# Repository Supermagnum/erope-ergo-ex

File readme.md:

# Europe-ergo
A 94 key ergonomic,split keyboard, panelized.
Its powered by 2X Raspberry pico and linked with two TRRS jacks.
It uses tht components.

The reset switches, TRRS jacks and raspberry pico's  goes on the reverse side of the Pcb's. 

or:
http://www.keyboard-layout-editor.com/#/gists/50db7ea7b0832342d4c734eb985ec16b

The L1/L2 button is to change from  Norwegian QWERTY to Norwegian Dvorak.

Keycaps:
https://github.com/Supermagnum/Europe-ergo/blob/main/keycaps.jpg

PCBway:

Aisler:
https://aisler.net/p/NEFSAHWJ

Firmware:
[https://github.com/Supermagnum/Europe-ergo/tree/main/Europe_ergo_firmware/europe_ergo](https://github.com/Supermagnum/Europe-ergo/tree/main/ergo-firmware/europe_ergo)

Picture:
https://github.com/Supermagnum/erope-ergo-ex/blob/main/Europe-flex.jpg

All mechanical blueprints as pdf files can be exported from the Freecad file.
Freecad can be found for free here:
https://www.freecadweb.org/

Vial:

https://get.vial.today/

PWM1 to PWM 4 controls LED's ( ON/OFF) based by the active layer, and also caps lock and scroll lock active.

Those and the electrical diagram can be found here:
https://github.com/Supermagnum/Europe-ergo/blob/main/Europe-ergo-PCB/schema/Europe-ergo.pdf
The right side has identical outputs for PWM.

Cherry MX switches should fit the PCB'S.

---------
To do:
Make the cutouts closer to the top and bottoms of the double rows.
Make pcb holders in kicad.
Reduce the number of two pin connectors, and label the connections on the Pcb's.

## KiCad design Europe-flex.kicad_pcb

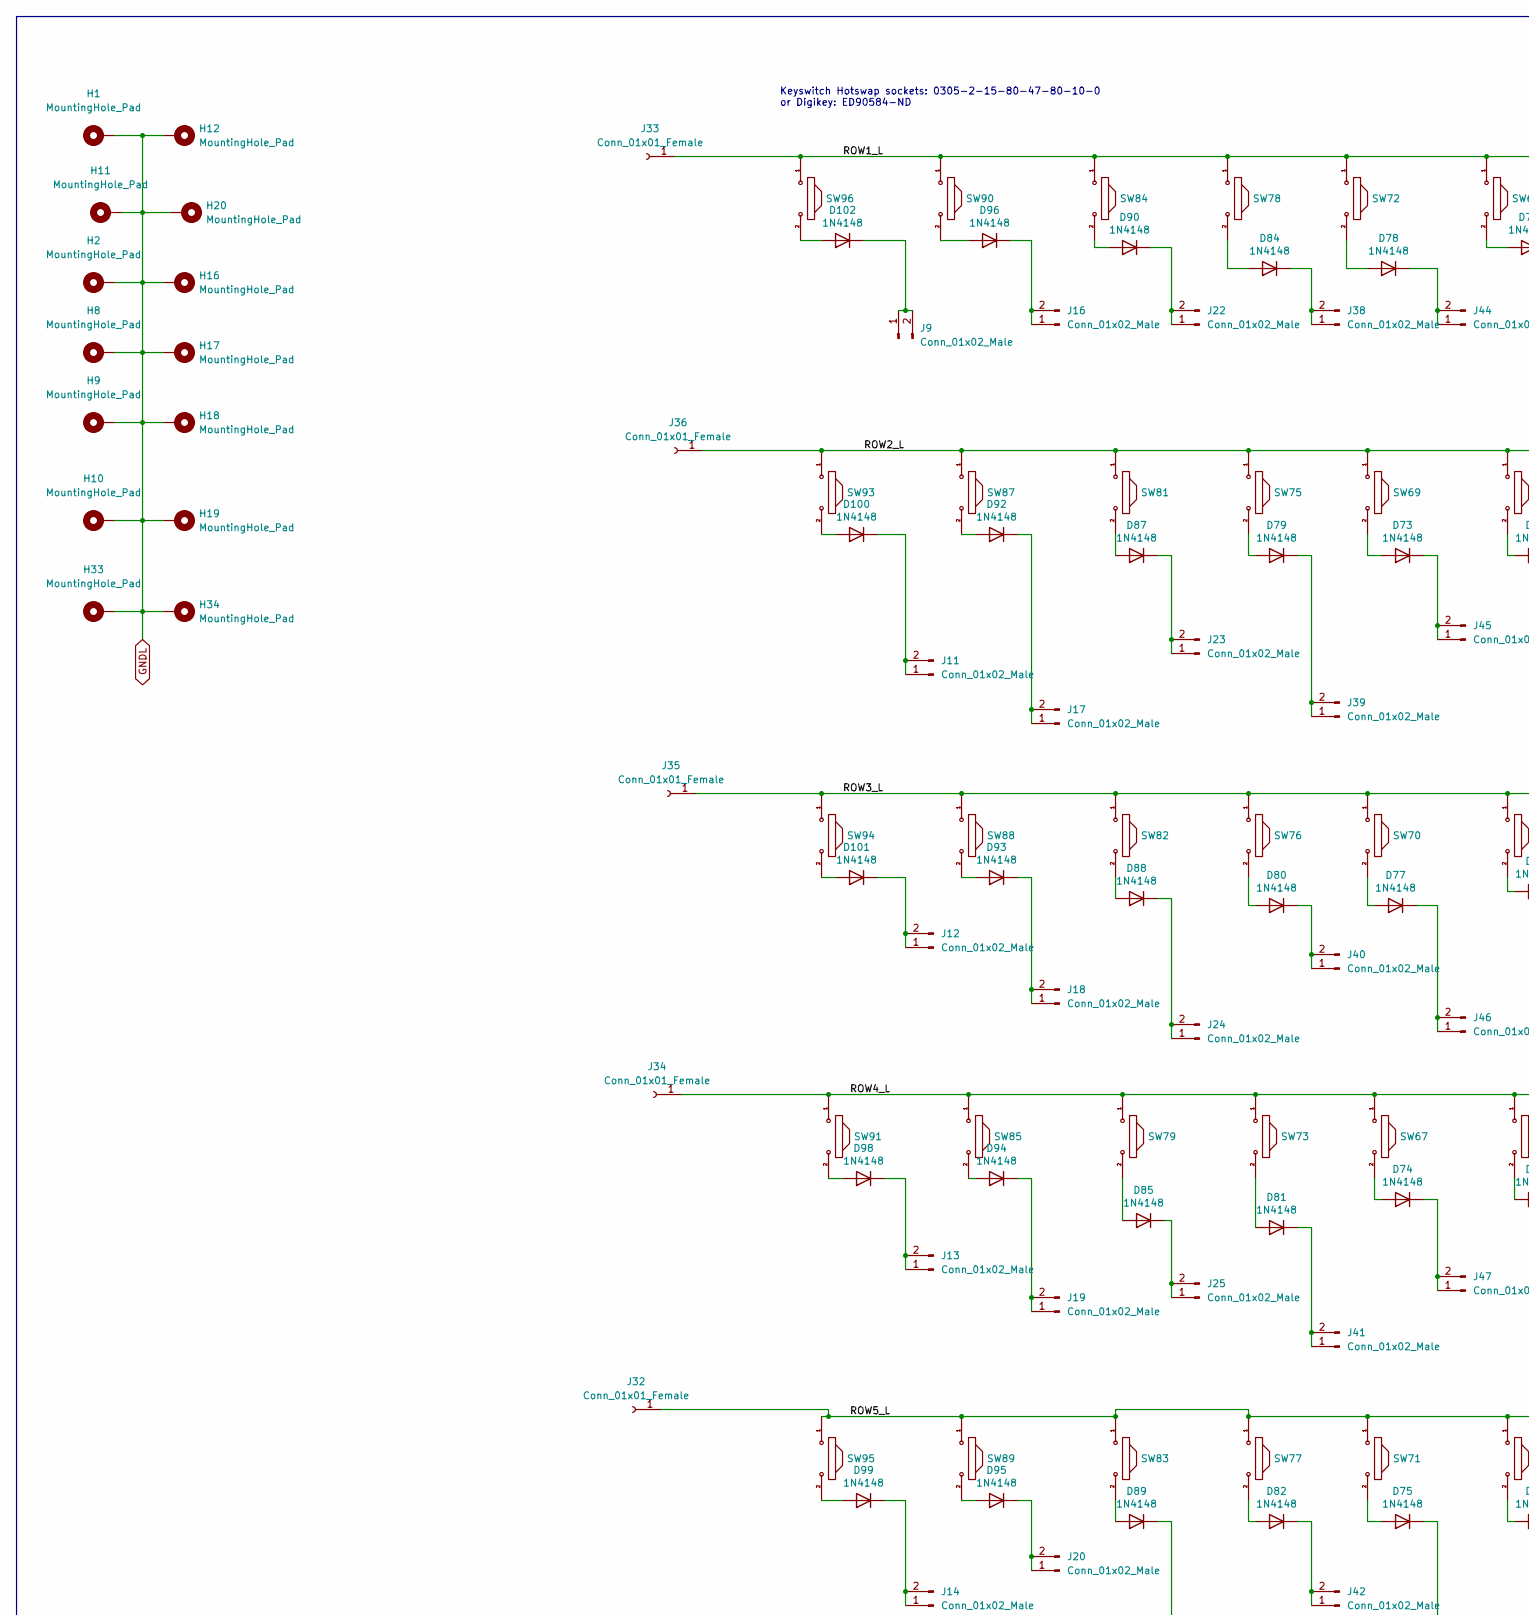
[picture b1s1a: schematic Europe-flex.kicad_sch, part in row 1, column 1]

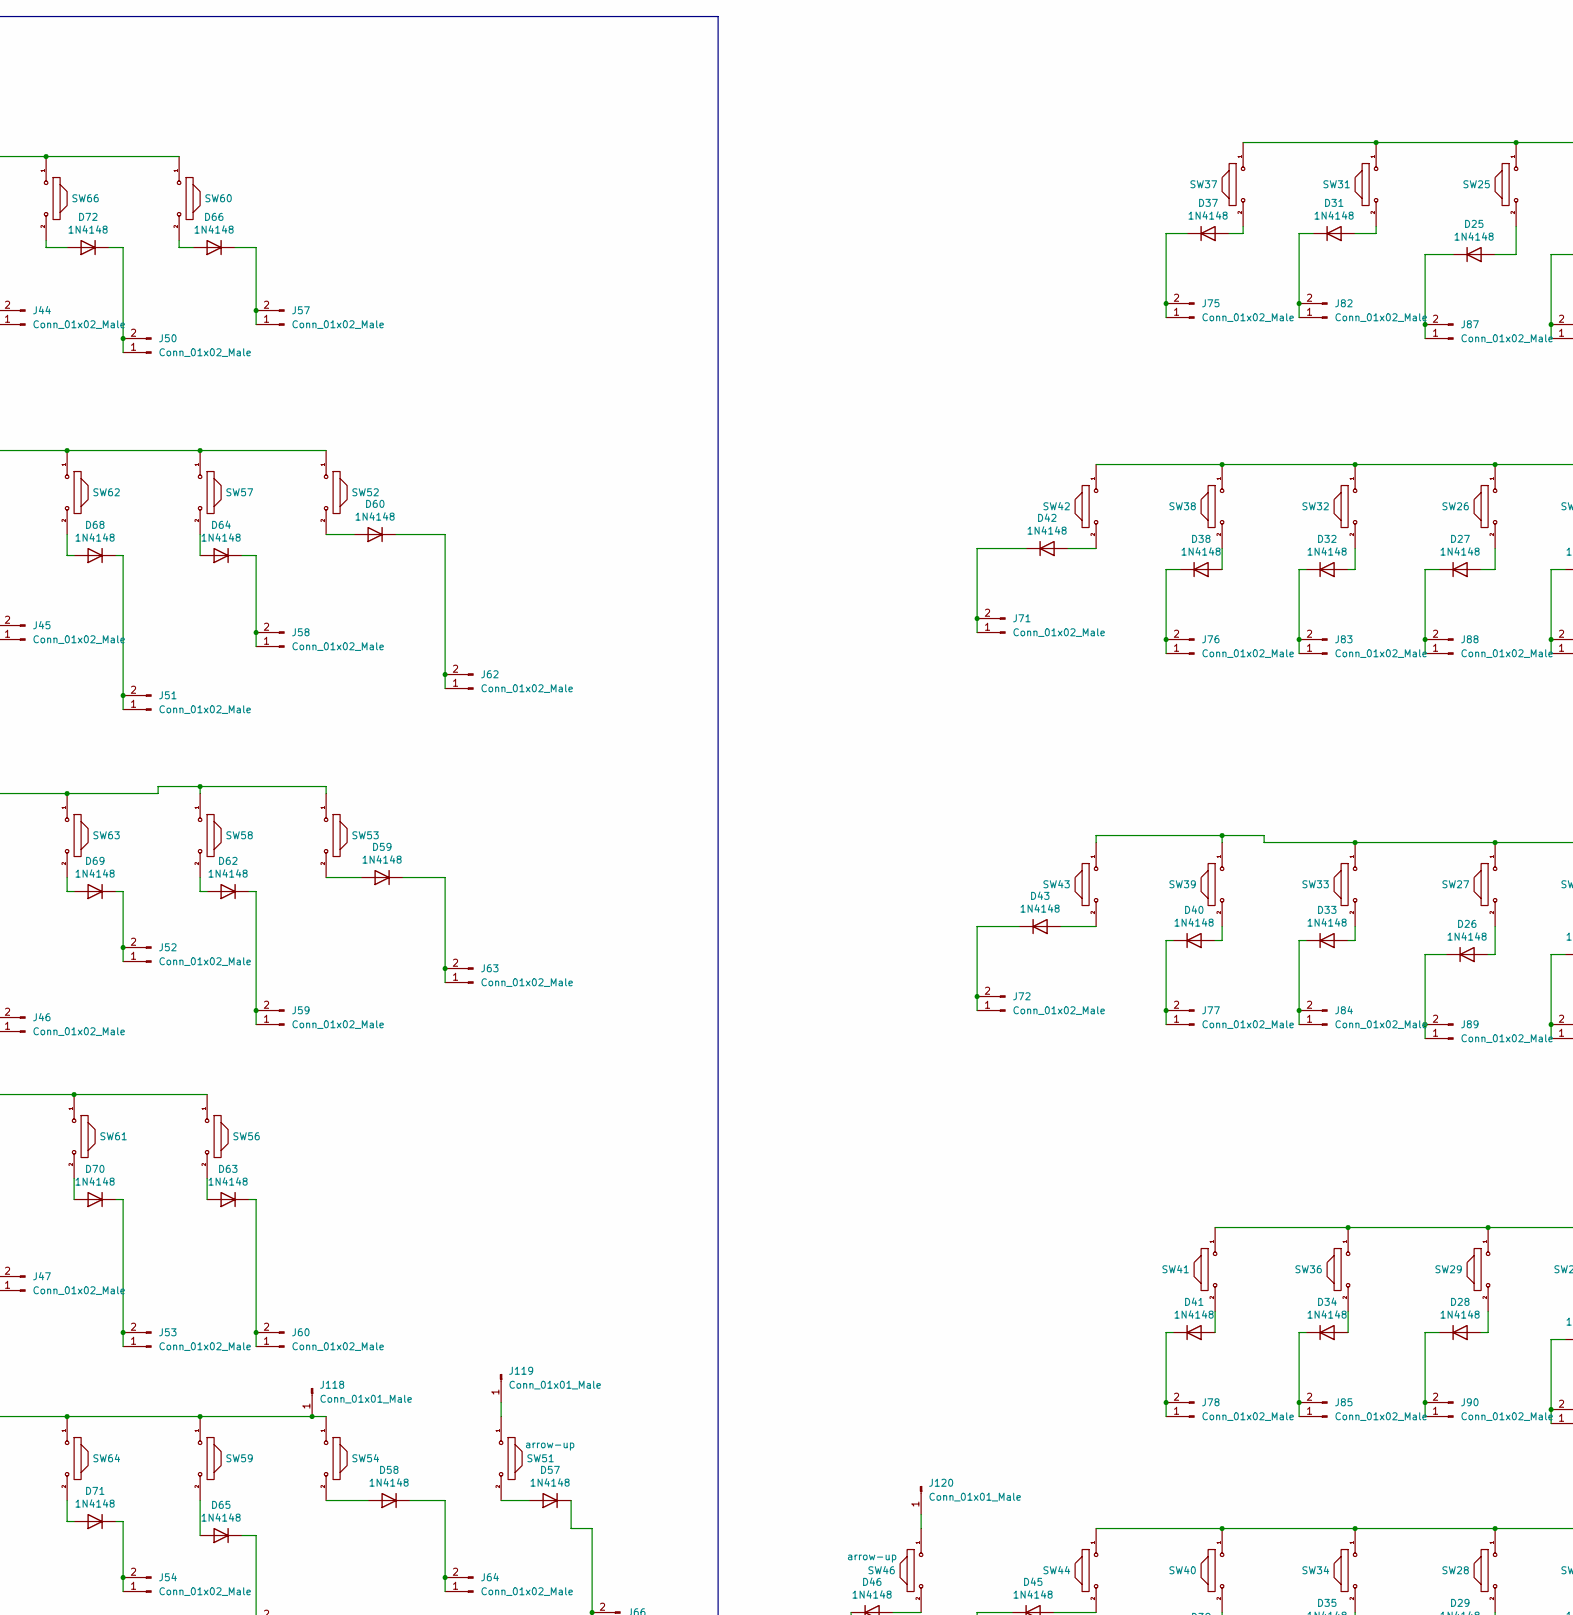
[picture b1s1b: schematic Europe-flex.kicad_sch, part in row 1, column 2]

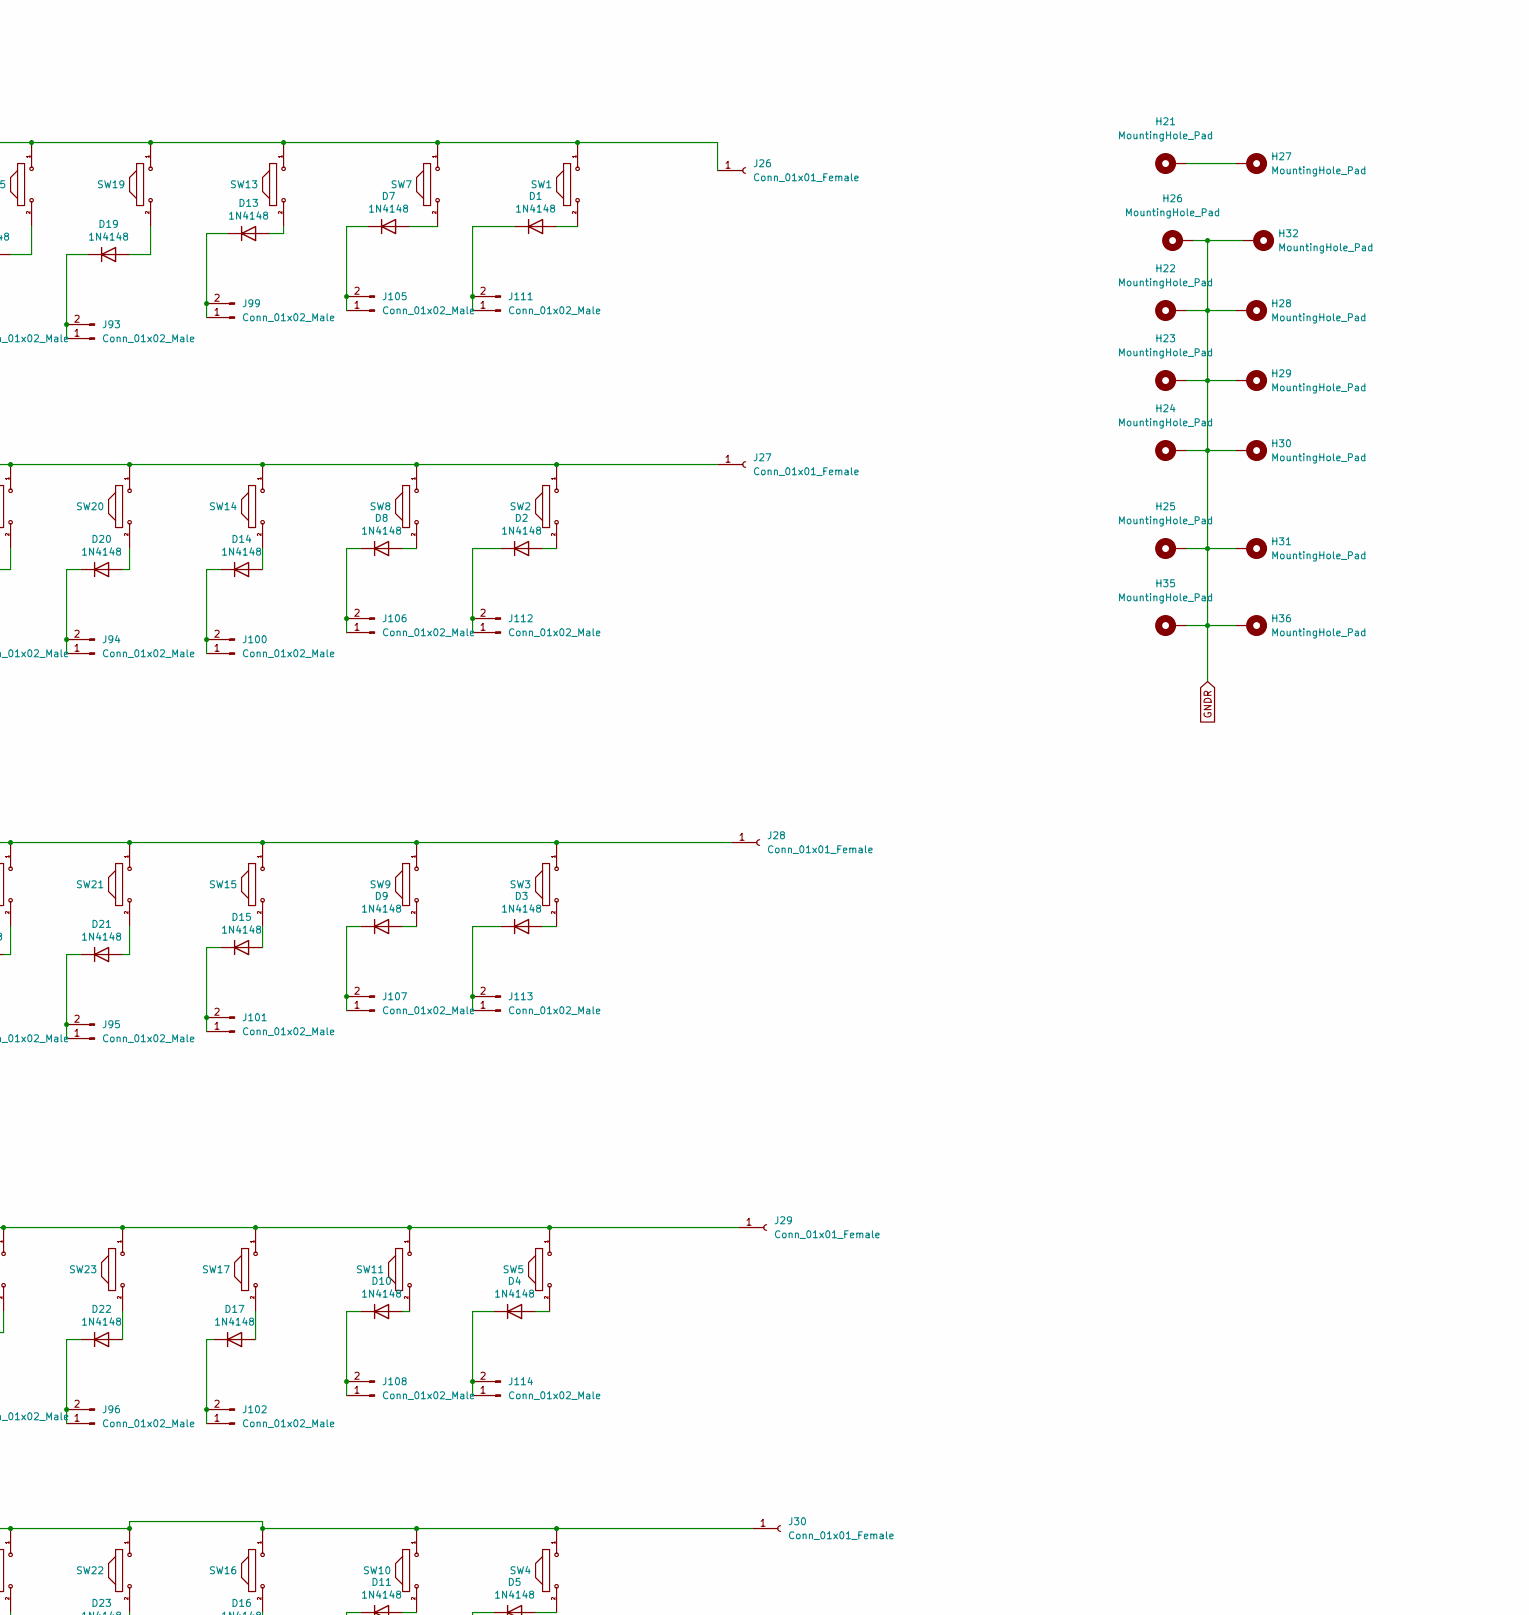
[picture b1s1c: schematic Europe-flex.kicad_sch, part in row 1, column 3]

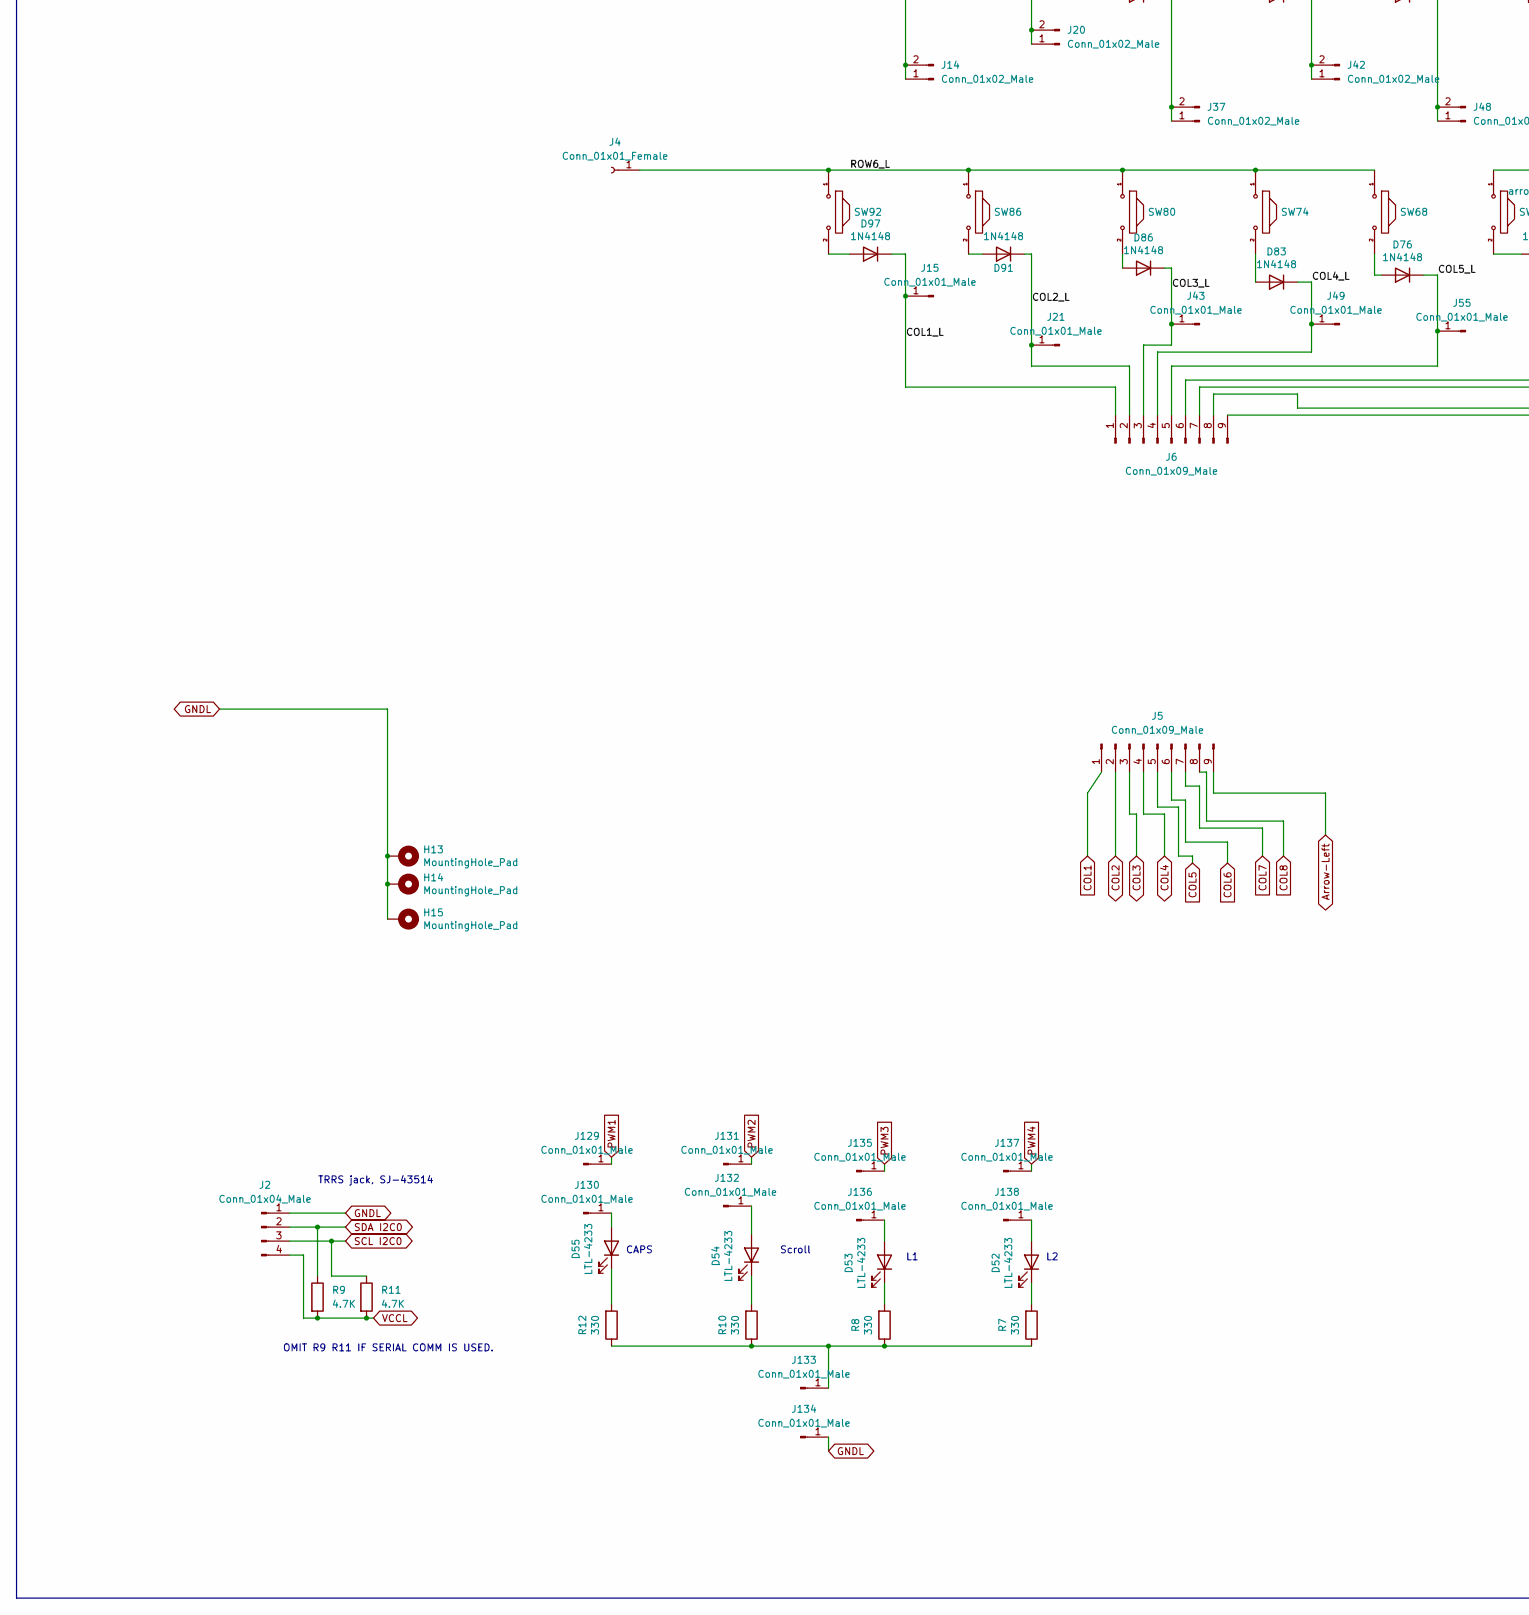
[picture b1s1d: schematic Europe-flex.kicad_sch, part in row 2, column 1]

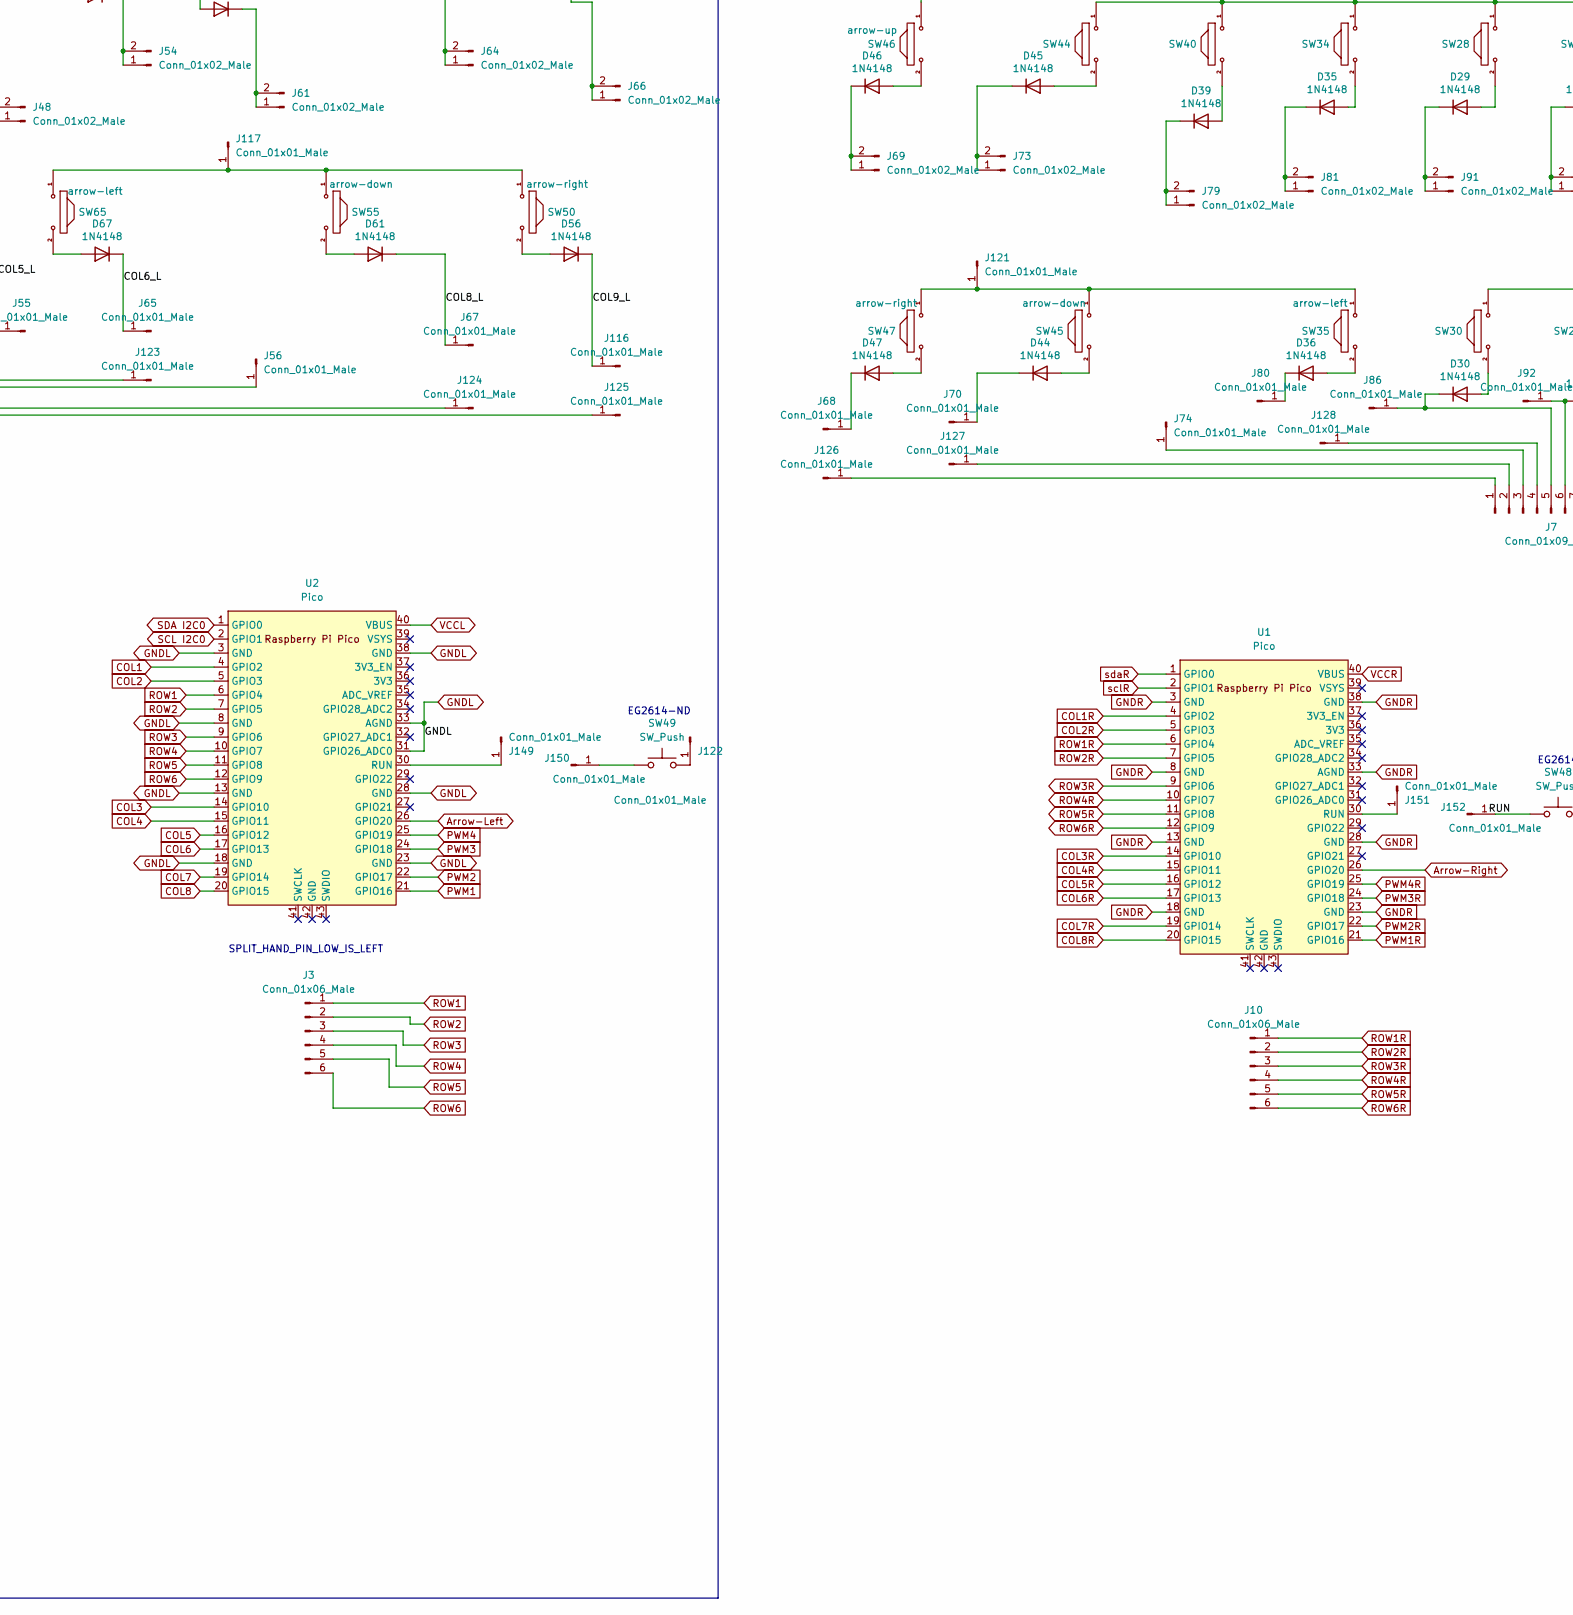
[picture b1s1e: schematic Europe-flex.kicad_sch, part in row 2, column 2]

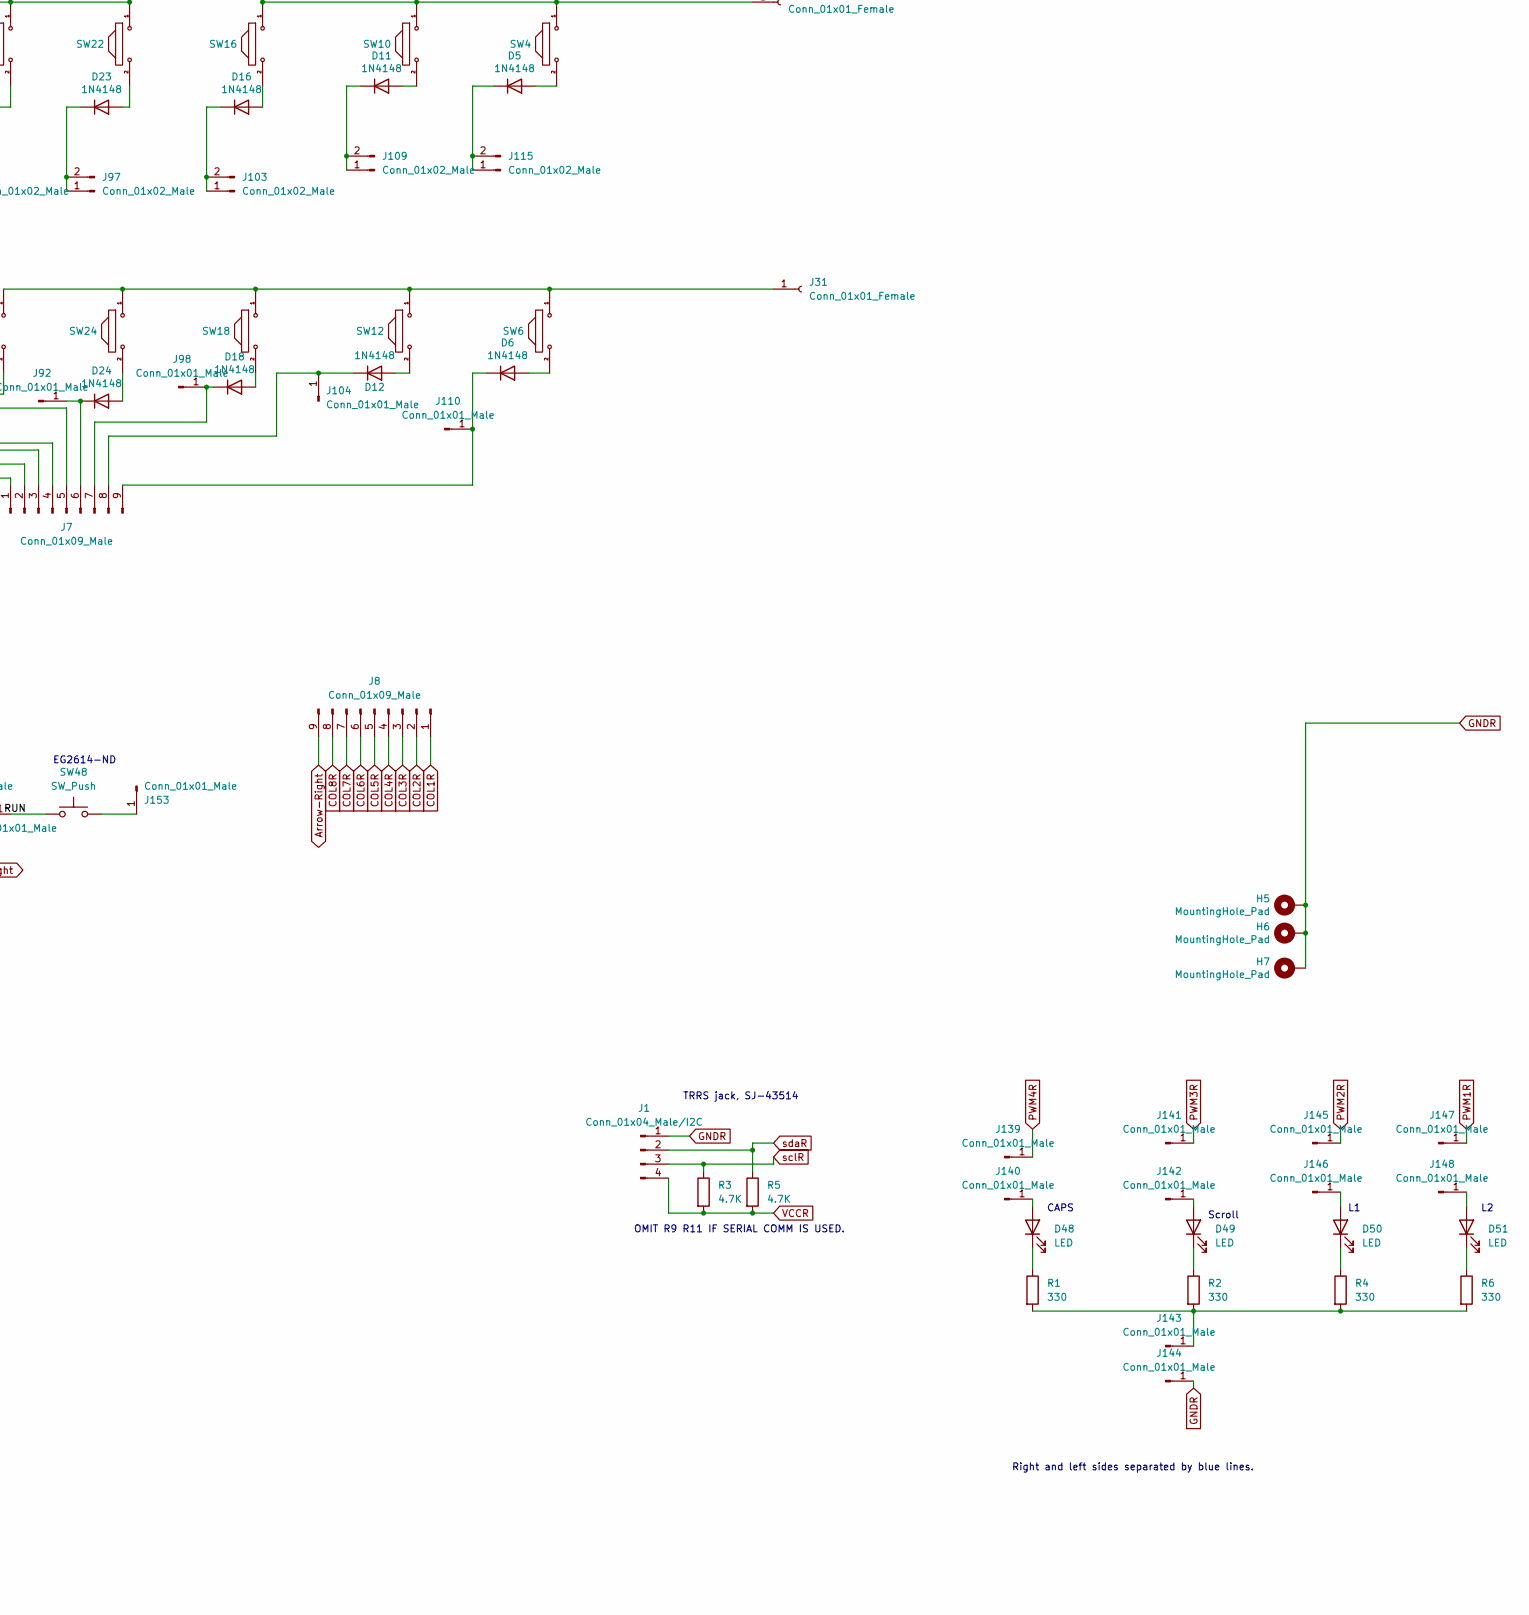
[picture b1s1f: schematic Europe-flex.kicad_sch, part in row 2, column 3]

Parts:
D1, D2, D3, D4, D5, D6, D7, D8, D9, D10, D11, D12, D13, D14, D15, D16, D17, D18, D19, D20, D21, D22, D23, D24, D25, D26, D27, D28, D29, D30, D31, D32, D33, D34, D35, D36, D37, D38, D39, D40, D41, D42, D43, D44, D45, D46, D47, D56, D57, D58, D59, D60, D61, D62, D63, D64, D65, D66, D67, D68, D69, D70, D71, D72, D73, D74, D75, D76, D77, D78, D79, D80, D81, D82, D83, D84, D85, D86, D87, D88, D89, D90, D91, D92, D93, D94, D95, D96, D97, D98, D99, D100, D101, D102: 1N4148; D_DO-35_SOD27_P7.62mm_Horizontal
D48, D49, D50, D51: LED; D_DO-34_SOD68_P2.54mm_Vertical_KathodeUp
D52, D53, D54, D55: LTL-4233; D_A-405_P2.54mm_Vertical_AnodeUp
H1, H2, H5, H6, H7, H8, H9, H10, H11, H12, H13, H14, H15, H16, H17, H18, H19, H20, H21, H22, H23, H24, H25, H26, H27, H28, H29, H30, H31, H32, H33, H34, H35, H36: MountingHole_Pad; MountingHole_4.3mm_M4_DIN965_Pad
J1: Conn_01x04_Male/I2C; CUI_SJ-43514
J2: Conn_01x04_Male; CUI_SJ-43514
J3, J10: Conn_01x06_Male; PinSocket_1x06_P2.54mm_Vertical
J4, J26, J27, J28, J29, J30, J31, J32, J33, J34, J35, J36: Conn_01x01_Female; PinSocket_1x01_P2.54mm_Vertical
J5, J6, J7, J8: Conn_01x09_Male; PinSocket_1x09_P2.54mm_Vertical
J9, J11, J12, J13, J14, J16, J17, J18, J19, J20, J22, J23, J24, J25, J37, J38, J39, J40, J41, J42, J44, J45, J46, J47, J48, J50, J51, J52, J53, J54, J57, J58, J59, J60, J61, J62, J63, J64, J66, J69, J71, J72, J73, J75, J76, J77, J78, J79, J81, J82, J83, J84, J85, J87, J88, J89, J90, J91, J93, J94, J95, J96, J97, J99, J100, J101, J102, J103, J105, J106, J107, J108, J109, J111, J112, J113, J114, J115: Conn_01x02_Male; PinHeader_1x02_P2.54mm_Vertical
J15, J21, J43, J49, J55, J56, J65, J67, J68, J70, J74, J80, J86, J92, J98, J104, J110, J116, J117, J118, J119, J120, J121, J122, J123, J124, J125, J126, J127, J128, J129, J130, J131, J132, J133, J134, J135, J136, J137, J138, J139, J140, J141, J142, J143, J144, J145, J146, J147, J148, J149, J150, J151, J152, J153: Conn_01x01_Male; PinHeader_1x01_P2.54mm_Vertical
R1, R2, R4, R6, R7, R8, R10, R12: 330; R_Axial_DIN0204_L3.6mm_D1.6mm_P5.08mm_Horizontal
R3, R5, R9, R11: 4.7K; R_Axial_DIN0204_L3.6mm_D1.6mm_P5.08mm_Horizontal
SW1, SW6, SW7, SW8, SW9, SW10, SW11, SW12, SW13, SW14, SW15, SW16, SW17, SW18, SW19, SW20, SW21, SW22, SW23, SW24, SW25, SW26, SW27, SW28, SW29, SW30, SW31, SW32, SW33, SW34, SW35, SW36, SW37, SW38, SW39, SW40, SW41, SW42, SW45, SW46, SW47, SW50, SW51, SW52, SW55, SW56, SW57, SW58, SW59, SW60, SW61, SW62, SW63, SW64, SW65, SW66, SW67, SW68, SW69, SW70, SW71, SW72, SW73, SW74, SW75, SW76, SW77, SW78, SW79, SW80, SW81, SW82, SW83, SW84, SW85, SW86, SW87, SW88, SW89, SW90, SW92, SW96: MX-NO-LED; SW_Cherry_MX_1.00u_PCB
SW2, SW3, SW4, SW5, SW43, SW44, SW53, SW54, SW91, SW93, SW94, SW95: MX-NO-LED; SW_Cherry_MX_1.50u_PCB
SW48, SW49: SW_Push; switch_P5.08mm
U1, U2: Pico; RPi_Pico_SMD_TH

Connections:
/COL1_L: D97.1 (K), J6.1, J15.1
/COL2_L: D91.1 (K), J6.2, J21.1
/COL3_L: D86.1 (K), J6.3, J43.1
/COL4_L: D83.1 (K), J6.4, J49.1
/COL5_L: D76.1 (K), J6.5, J55.1
/COL6_L: D67.1 (K), J65.1
/COL8_L: D61.1 (K), J67.1
/COL9_L: D56.1 (K), J116.1
/ROW1_L: J33.1, SW60.1, SW66.1, SW72.1, SW78.1, SW84.1, SW90.1, SW96.1
/ROW2_L: J36.1, SW52.1, SW57.1, SW62.1, SW69.1, SW75.1, SW81.1, SW87.1, SW93.1
/ROW3_L: J35.1, SW53.1, SW58.1, SW63.1, SW70.1, SW76.1, SW82.1, SW88.1, SW94.1
/ROW4_L: J34.1, SW56.1, SW61.1, SW67.1, SW73.1, SW79.1, SW85.1, SW91.1
/ROW5_L: J32.1, J118.1, SW54.1, SW59.1, SW64.1, SW71.1, SW77.1, SW83.1, SW89.1, SW95.1
/ROW6_L: J4.1, SW68.1, SW74.1, SW80.1, SW86.1, SW92.1
Arrow-Left: J5.9, U2.26 (GPIO20)
Arrow-Right: J8.9, U1.26 (GPIO20)
COL1: J5.1, U2.4 (GPIO2)
COL1R: J8.1, U1.4 (GPIO2)
COL2: J5.2, U2.5 (GPIO3)
COL2R: J8.2, U1.5 (GPIO3)
COL3: J5.3, U2.14 (GPIO10)
COL3R: J8.3, U1.14 (GPIO10)
COL4: J5.4, U2.15 (GPIO11)
COL4R: J8.4, U1.15 (GPIO11)
COL5: J5.5, U2.16 (GPIO12)
COL5R: J8.5, U1.16 (GPIO12)
COL6: J5.6, U2.17 (GPIO13)
COL6R: J8.6, U1.17 (GPIO13)
COL7: J5.7, U2.19 (GPIO14)
COL7R: J8.7, U1.19 (GPIO14)
COL8: J5.8, U2.20 (GPIO15)
COL8R: J8.8, U1.20 (GPIO15)
unnamed: D1.1 (K), J111.1, J111.2
unnamed: D1.2 (A), SW1.2
unnamed: D2.1 (K), J112.1, J112.2
unnamed: D2.2 (A), SW2.2
unnamed: D3.1 (K), J113.1, J113.2
unnamed: D3.2 (A), SW3.2
unnamed: D4.1 (K), J114.1, J114.2
unnamed: D4.2 (A), SW5.2
unnamed: D5.1 (K), J115.1, J115.2
unnamed: D5.2 (A), SW4.2
unnamed: D6.1 (K), J7.9, J110.1
unnamed: D6.2 (A), SW6.2
unnamed: D7.1 (K), J105.1, J105.2
unnamed: D7.2 (A), SW7.2
unnamed: D8.1 (K), J106.1, J106.2
unnamed: D8.2 (A), SW8.2
unnamed: D9.1 (K), J107.1, J107.2
unnamed: D9.2 (A), SW9.2
unnamed: D10.1 (K), J108.1, J108.2
unnamed: D10.2 (A), SW11.2
unnamed: D11.1 (K), J109.1, J109.2
unnamed: D11.2 (A), SW10.2
unnamed: D12.1 (K), J7.8, J104.1
unnamed: D12.2 (A), SW12.2
unnamed: D13.1 (K), J99.1, J99.2
unnamed: D13.2 (A), SW13.2
unnamed: D14.1 (K), J100.1, J100.2
unnamed: D14.2 (A), SW14.2
unnamed: D15.1 (K), J101.1, J101.2
unnamed: D15.2 (A), SW15.2
unnamed: D16.1 (K), J103.1, J103.2
unnamed: D16.2 (A), SW16.2
unnamed: D17.1 (K), J102.1, J102.2
unnamed: D17.2 (A), SW17.2
unnamed: D18.1 (K), J7.7, J98.1
unnamed: D18.2 (A), SW18.2
unnamed: D19.1 (K), J93.1, J93.2
unnamed: D19.2 (A), SW19.2
unnamed: D20.1 (K), J94.1, J94.2
unnamed: D20.2 (A), SW20.2
unnamed: D21.1 (K), J95.1, J95.2
unnamed: D21.2 (A), SW21.2
unnamed: D22.1 (K), J96.1, J96.2
unnamed: D22.2 (A), SW23.2
unnamed: D23.1 (K), J97.1, J97.2
unnamed: D23.2 (A), SW22.2
unnamed: D24.1 (K), J7.6, J92.1
unnamed: D24.2 (A), SW24.2
unnamed: D25.1 (K), J87.1, J87.2
unnamed: D25.2 (A), SW25.2
unnamed: D26.1 (K), J89.1, J89.2
unnamed: D26.2 (A), SW27.2
unnamed: D27.1 (K), J88.1, J88.2
unnamed: D27.2 (A), SW26.2
unnamed: D28.1 (K), J90.1, J90.2
unnamed: D28.2 (A), SW29.2
unnamed: D29.1 (K), J91.1, J91.2
unnamed: D29.2 (A), SW28.2
unnamed: D30.1 (K), J7.5, J86.1
unnamed: D30.2 (A), SW30.2
unnamed: D31.1 (K), J82.1, J82.2
unnamed: D31.2 (A), SW31.2
unnamed: D32.1 (K), J83.1, J83.2
unnamed: D32.2 (A), SW32.2
unnamed: D33.1 (K), J84.1, J84.2
unnamed: D33.2 (A), SW33.2
unnamed: D34.1 (K), J85.1, J85.2
unnamed: D34.2 (A), SW36.2
unnamed: D35.1 (K), J81.1, J81.2
unnamed: D35.2 (A), SW34.2
unnamed: D36.1 (K), J80.1
unnamed: D36.2 (A), SW35.2
unnamed: D37.1 (K), J75.1, J75.2
unnamed: D37.2 (A), SW37.2
unnamed: D38.1 (K), J76.1, J76.2
unnamed: D38.2 (A), SW38.2
unnamed: D39.1 (K), J79.1, J79.2
unnamed: D39.2 (A), SW40.2
unnamed: D40.1 (K), J77.1, J77.2
unnamed: D40.2 (A), SW39.2
unnamed: D41.1 (K), J78.1, J78.2
unnamed: D41.2 (A), SW41.2
unnamed: D42.1 (K), J71.1, J71.2
unnamed: D42.2 (A), SW42.2
unnamed: D43.1 (K), J72.1, J72.2
unnamed: D43.2 (A), SW43.2
unnamed: D44.1 (K), J70.1
unnamed: D44.2 (A), SW45.2
unnamed: D45.1 (K), J73.1, J73.2
unnamed: D45.2 (A), SW44.2
unnamed: D46.1 (K), J69.1, J69.2
unnamed: D46.2 (A), SW46.2
unnamed: D47.1 (K), J68.1
unnamed: D47.2 (A), SW47.2
unnamed: D48.1 (K), R1.1
unnamed: D48.2 (A), J140.1
unnamed: D49.1 (K), R2.1
unnamed: D49.2 (A), J142.1
unnamed: D50.1 (K), R4.1
unnamed: D50.2 (A), J146.1
unnamed: D51.1 (K), R6.1
unnamed: D51.2 (A), J148.1
unnamed: D52.1 (K), R7.2
unnamed: D52.2 (A), J138.1
unnamed: D53.1 (K), R8.2
unnamed: D53.2 (A), J136.1
unnamed: D54.1 (K), R10.2
unnamed: D54.2 (A), J132.1
unnamed: D55.1 (K), R12.2
unnamed: D55.2 (A), J130.1
unnamed: D56.2 (A), SW50.2
unnamed: D57.1 (K), J66.1, J66.2
unnamed: D57.2 (A), SW51.2
unnamed: D58.1 (K), J64.1, J64.2
unnamed: D58.2 (A), SW54.2
unnamed: D59.1 (K), J63.1, J63.2
unnamed: D59.2 (A), SW53.2
unnamed: D60.1 (K), J62.1, J62.2
unnamed: D60.2 (A), SW52.2
unnamed: D61.2 (A), SW55.2
unnamed: D62.1 (K), J59.1, J59.2
unnamed: D62.2 (A), SW58.2
unnamed: D63.1 (K), J60.1, J60.2
unnamed: D63.2 (A), SW56.2
unnamed: D64.1 (K), J58.1, J58.2
unnamed: D64.2 (A), SW57.2
unnamed: D65.1 (K), J61.1, J61.2
unnamed: D65.2 (A), SW59.2
unnamed: D66.1 (K), J57.1, J57.2
unnamed: D66.2 (A), SW60.2
unnamed: D67.2 (A), SW65.2
unnamed: D68.1 (K), J51.1, J51.2
unnamed: D68.2 (A), SW62.2
unnamed: D69.1 (K), J52.1, J52.2
unnamed: D69.2 (A), SW63.2
unnamed: D70.1 (K), J53.1, J53.2
unnamed: D70.2 (A), SW61.2
unnamed: D71.1 (K), J54.1, J54.2
unnamed: D71.2 (A), SW64.2
unnamed: D72.1 (K), J50.1, J50.2
unnamed: D72.2 (A), SW66.2
unnamed: D73.1 (K), J45.1, J45.2
unnamed: D73.2 (A), SW69.2
unnamed: D74.1 (K), J47.1, J47.2
unnamed: D74.2 (A), SW67.2
unnamed: D75.1 (K), J48.1, J48.2
unnamed: D75.2 (A), SW71.2
unnamed: D76.2 (A), SW68.2
unnamed: D77.1 (K), J46.1, J46.2
unnamed: D77.2 (A), SW70.2
unnamed: D78.1 (K), J44.1, J44.2
unnamed: D78.2 (A), SW72.2
unnamed: D79.1 (K), J39.1, J39.2
unnamed: D79.2 (A), SW75.2
unnamed: D80.1 (K), J40.1, J40.2
unnamed: D80.2 (A), SW76.2
unnamed: D81.1 (K), J41.1, J41.2
unnamed: D81.2 (A), SW73.2
unnamed: D82.1 (K), J42.1, J42.2
unnamed: D82.2 (A), SW77.2
unnamed: D83.2 (A), SW74.2
unnamed: D84.1 (K), J38.1, J38.2
unnamed: D84.2 (A), SW78.2
unnamed: D85.1 (K), J25.1, J25.2
unnamed: D85.2 (A), SW79.2
unnamed: D86.2 (A), SW80.2
unnamed: D87.1 (K), J23.1, J23.2
unnamed: D87.2 (A), SW81.2
unnamed: D88.1 (K), J24.1, J24.2
unnamed: D88.2 (A), SW82.2
unnamed: D89.1 (K), J37.1, J37.2
unnamed: D89.2 (A), SW83.2
unnamed: D90.1 (K), J22.1, J22.2
unnamed: D90.2 (A), SW84.2
unnamed: D91.2 (A), SW86.2
unnamed: D92.1 (K), J17.1, J17.2
unnamed: D92.2 (A), SW87.2
unnamed: D93.1 (K), J18.1, J18.2
unnamed: D93.2 (A), SW88.2
unnamed: D94.1 (K), J19.1, J19.2
unnamed: D94.2 (A), SW85.2
unnamed: D95.1 (K), J20.1, J20.2
unnamed: D95.2 (A), SW89.2
unnamed: D96.1 (K), J16.1, J16.2
unnamed: D96.2 (A), SW90.2
unnamed: D97.2 (A), SW92.2
unnamed: D98.1 (K), J13.1, J13.2
unnamed: D98.2 (A), SW91.2
unnamed: D99.1 (K), J14.1, J14.2
unnamed: D99.2 (A), SW95.2
unnamed: D100.1 (K), J11.1, J11.2
unnamed: D100.2 (A), SW93.2
unnamed: D101.1 (K), J12.1, J12.2
unnamed: D101.2 (A), SW94.2
unnamed: D102.1 (K), J9.1, J9.2
unnamed: D102.2 (A), SW96.2
unnamed: H21.1, H27.1
unnamed: J7.3, J74.1
unnamed: J26.1, SW1.1, SW7.1, SW13.1, SW19.1, SW25.1, SW31.1, SW37.1
unnamed: J27.1, SW2.1, SW8.1, SW14.1, SW20.1, SW26.1, SW32.1, SW38.1, SW42.1
unnamed: J28.1, SW3.1, SW9.1, SW15.1, SW21.1, SW27.1, SW33.1, SW39.1, SW43.1
unnamed: J29.1, SW5.1, SW11.1, SW17.1, SW23.1, SW29.1, SW36.1, SW41.1
unnamed: J30.1, SW4.1, SW10.1, SW16.1, SW22.1, SW28.1, SW34.1, SW40.1, SW44.1
unnamed: J31.1, SW6.1, SW12.1, SW18.1, SW24.1, SW30.1
unnamed: J6.7, J56.1
unnamed: J117.1, SW50.1, SW55.1, SW65.1
unnamed: J119.1, SW51.1
unnamed: J120.1, SW46.1
unnamed: J121.1, SW35.1, SW45.1, SW47.1
unnamed: J122.1, SW49.2
unnamed: J6.6, J123.1
unnamed: J6.8, J124.1
unnamed: J6.9, J125.1
unnamed: J7.1, J126.1
unnamed: J7.2, J127.1
unnamed: J7.4, J128.1
unnamed: J133.1, R7.1, R8.1, R10.1, R12.1
unnamed: J143.1, R1.2, R2.2, R4.2, R6.2
unnamed: J149.1, U2.30 (RUN)
unnamed: J150.1, SW49.1
unnamed: J151.1, U1.30 (RUN)
unnamed: J152.1, SW48.1
unnamed: J153.1, SW48.2
PWM1: J129.1, U2.21 (GPIO16)
PWM1R: J147.1, U1.21 (GPIO16)
PWM2: J131.1, U2.22 (GPIO17)
PWM2R: J145.1, U1.22 (GPIO17)
PWM3: J135.1, U2.24 (GPIO18)
PWM3R: J141.1, U1.24 (GPIO18)
PWM4: J137.1, U2.25 (GPIO19)
PWM4R: J139.1, U1.25 (GPIO19)
ROW1: J3.1, U2.6 (GPIO4)
ROW1R: J10.1, U1.6 (GPIO4)
ROW2: J3.2, U2.7 (GPIO5)
ROW2R: J10.2, U1.7 (GPIO5)
ROW3: J3.3, U2.9 (GPIO6)
ROW3R: J10.3, U1.9 (GPIO6)
ROW4: J3.4, U2.10 (GPIO7)
ROW4R: J10.4, U1.10 (GPIO7)
ROW5: J3.5, U2.11 (GPIO8)
ROW5R: J10.5, U1.11 (GPIO8)
ROW6: J3.6, U2.12 (GPIO9)
ROW6R: J10.6, U1.12 (GPIO9)
SCL I2C0: J2.3, R11.1, U2.2 (GPIO1)
SDA I2C0: J2.2, R9.1, U2.1 (GPIO0)
VCCL: J2.4, R9.2, R11.2, U2.40 (VBUS)
VCCR: J1.4, R3.2, R5.2, U1.40 (VBUS)
sclR: J1.3, R3.1, U1.2 (GPIO1)
sdaR: J1.2, R5.1, U1.1 (GPIO0)

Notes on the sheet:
EG2614-ND
Keyswitch Hotswap sockets: 0305-2-15-80-47-80-10-0 or Digikey: ED90584-ND
CAPS
Right and left sides separated by blue lines.
Scroll
OMIT R9 R11 IF SERIAL COMM IS USED.
SPLIT_HAND_PIN_LOW_IS_LEFT
TRRS jack, SJ-43514

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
